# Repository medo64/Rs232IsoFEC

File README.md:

[Isolated RS-232 Framework Expansion Card](https://medo64.com/rs232isofec/)
===========================================================================

This Framework laptop expansion card will show up on your system as a serial
device and allow for isolated RS-232 communication up to 460,800 baud rate.

## UART Pinout

To connect to this board, one has to use a 5-pin JST XH connector. The following
table represents the pinout, pin 1 being on the left as looking into the
expansion card. Note that pins 1 and 5 are not internally connected.

| # | Ref | Description                     | DB9 |
|--:|:---:|---------------------------------|----:|
| 1 |  -  | Not connected                   |  8  |
| 2 | RXD | Receive data                    |  2  |
| 3 | GND | Ground connection               |  5  |
| 4 | TXD | Transmit data                   |  3  |
| 5 |  -  | Not connected                   |  7  |

As power consumption is low, wires can be almost any AWG. I would recommend
using 24 AWG wire 0.25 mm² as they allow for greater compatibility with other
connectors.

## Supported Speeds

This board employs the FT232R as its UART chip, and consequently, it supports
all the baud rates this chip [can handle](https://ftdichip.com/Documents/AppNotes/AN232B-05_BaudRates.pdf)
up to 460,800 baud which is the limit of isolator chip used. The table below
lists the standard baud rates.

| Baud rate |    Actual | Error |    Divisor |
|----------:|----------:|------:|-----------:|
|       300 |       300 | 0.00% |  10000.000 |
|       600 |       600 | 0.00% |   5000.000 |
|     1,200 |     1,200 | 0.00% |   2500.000 |
|     1,800 |     1,800 | 0.00% |   1666.625 |
|     2,400 |     2,400 | 0.00% |   1250.000 |
|     4,800 |     4,800 | 0.00% |    625.000 |
|     7,200 |     7,201 | 0.01% |    416.625 |
|     9,600 |     9,600 | 0.00% |    312.500 |
|    14,400 |    14,406 | 0.04% |    208.250 |
|    19,200 |    19,200 | 0.00% |    156.250 |
|    28,800 |    28,812 | 0.04% |    104.125 |
|    38,400 |    38,400 | 0.00% |     78.125 |
|    57,600 |    57,692 | 0.16% |     52.000 |
|   115,200 |   115,385 | 0.16% |     26.000 |
|   230,400 |   230,769 | 0.16% |     13.000 |
|   460,800 |   461,538 | 0.16% |      6.500 |

While rates above this can be set, they are not guaranteed to work.

---
*You can check my blog and other projects at [www.medo64.com](https://www.medo64.com/electronics/).*

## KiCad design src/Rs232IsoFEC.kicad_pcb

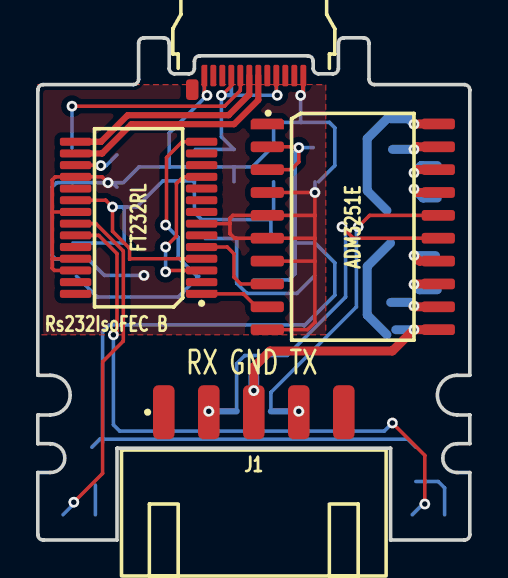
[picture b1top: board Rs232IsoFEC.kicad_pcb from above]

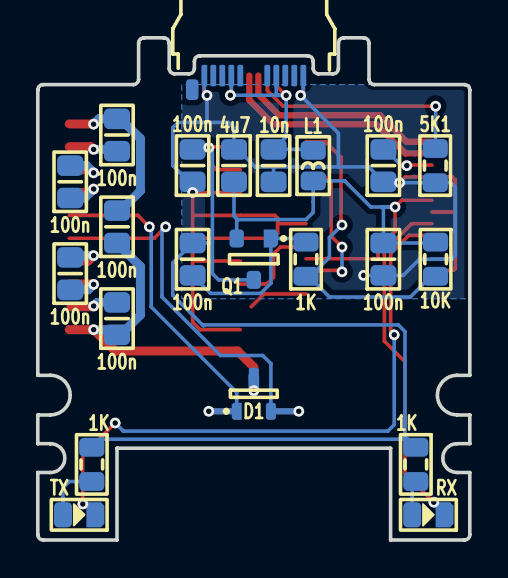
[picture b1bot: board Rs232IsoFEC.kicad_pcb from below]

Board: 2 copper layers, 24.0 x 27.9 mm, 25 parts (21 on the bottom side), 27 nets.

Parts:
C1: 10n; C (0805)
C2, C3, C4, C5, C6, C7, C8, C9, C10: 100n; C (0805)
C11: 4u7; C (0805)
D1: PESD12VL2BT; D TVS SM05T1G (SOT23-3)
DS1: RX; DS (0805)
DS2: TX; DS (0805)
J1: B5B-XH-A; J JST XH Edge [UART] (5w)
L1: 600R; L (0805)
P1: 105444-0001; P USB C 3.2 Edge (24w)
Q1: DMP3099L-13; Q MOSFET-P (SOT23-3)
R1, R2, R3: 1K; R (0805)
R4: 5K1; R (0805)
R5: 10K; R (0805)
U1: FT232RL; U Transciever UART FT232RL (SSOP-28)
U2: ADM3251E; U Transciever RS232 Isolated ADM3251E (SOIC-20)

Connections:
3V3: C3.2, U1.17
5V: C2.2, C11.2, L1.1, Q1.2, R5.1, U1.4, U1.20
5V_SW: C4.2, C10.2, Q1.3, R1.1, R2.1, U2.2, U2.3
A_CC: P1.A5, R4.2
GND: C1.1, C2.1, C3.1, C4.1, C11.1, P1.A1, P1.A12, P1.B01, P1.B12, R4.1, U1.7, U1.18, U1.21, U1.25, U1.26, U2.4, U2.5, U2.6, U2.7, U2.10
ISO_C1+: C6.2, U2.18
ISO_C1-: C6.1, U2.17
ISO_C2+: C8.2, U2.14
ISO_C2-: C8.1, U2.13
ISO_GND: C7.1, C9.1, D1.3, J1.3, U2.11
ISO_RXD: D1.2, J1.2, U2.15
ISO_TXD: D1.1, J1.4, U2.16
ISO_V+: C5.1, U2.19
ISO_V-: C9.2, U2.12
ISO_Viso: C5.2, C7.2, U2.20
LED_RXD: DS1.1, U1.22
LED_RXD': DS1.2, R1.2
LED_TXD: DS2.1, U1.23
LED_TXD': DS2.2, R2.2
PWREN#: R3.1, R5.2, U1.14
PWREN#': C10.1, Q1.1, R3.2
RTS_CTS: U1.3, U1.11
RXD: U1.5, U2.8
TXD: U1.1, U2.9
USB_DM: P1.A7, U1.16
USB_DP: P1.A6, U1.15
USB_Vin: C1.2, L1.2, P1.A4, P1.A9, P1.B04, P1.B09

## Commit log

2023-11-02 Added mosfet to turn off isolator in sleep mode
2023-11-03 Added soft-start capacitor for isolator
2023-11-03 Adjusted FTDI config file
2023-11-03 Updated protection diode to 12V
2023-11-04 Added RTS/CTS loopback
2023-11-13 Changed protection diode
2023-11-13 Minor refactoring
2023-11-13 Moved LEDs to bottom
2023-12-26 Added PWREN pullup and moved LED 5V to switched
2023-12-26 Changed conntector to 5-pin variant
2023-12-30 Refactoring copper pour
2024-01-06 Added DB-9 pinput
2024-01-31 Moved board RefDes to top
